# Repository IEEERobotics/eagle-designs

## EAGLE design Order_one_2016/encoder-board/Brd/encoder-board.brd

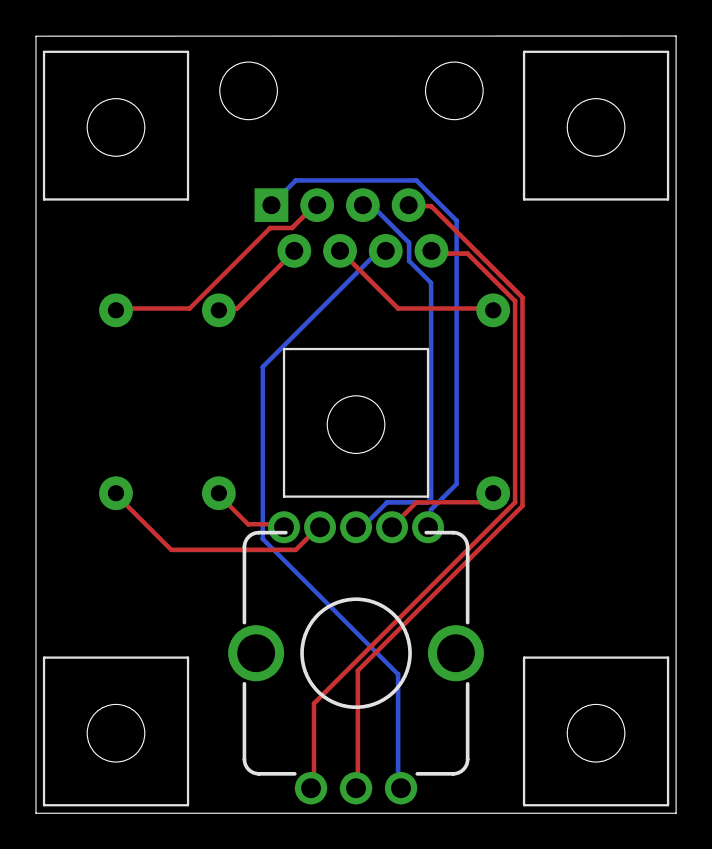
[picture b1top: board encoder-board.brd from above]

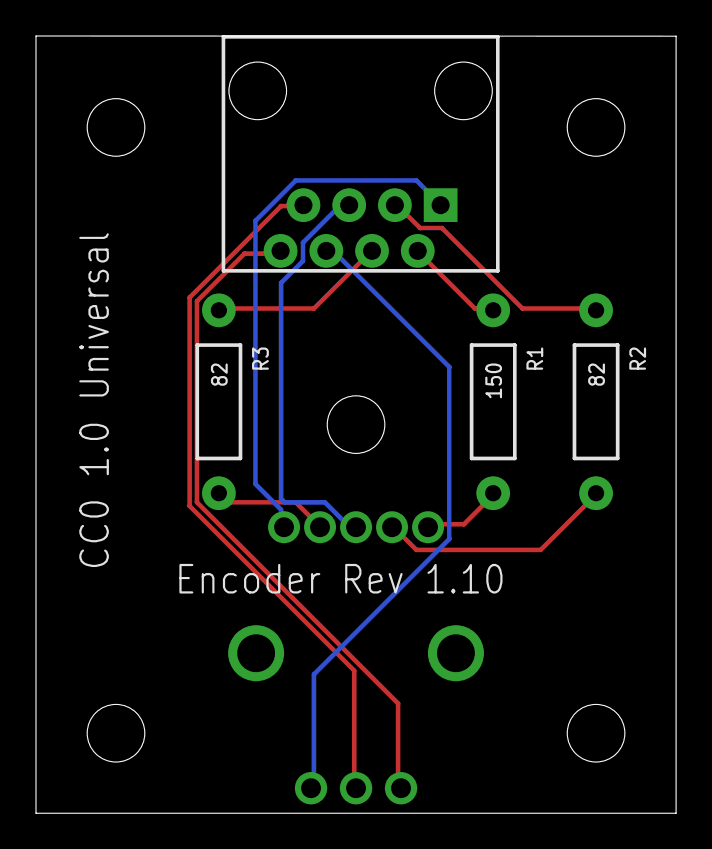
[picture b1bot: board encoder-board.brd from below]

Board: 2 copper layers, 35.6 x 43.2 mm, 10 parts (4 on the bottom side), 11 nets.

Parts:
J1: RJ45-8PTH; RJ45-8
MT1, MT2, MT3, MT4, MT5: 3.2-MOUNT
R1: 150; AXIAL-0.4
R2, R3: 82; AXIAL-0.4
SW2: SPARKFUN-COM-10982; ENCODER_LED_3

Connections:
BLUE: J1.4, R3.P$1
GREEN: J1.3, R2.P$1
LED-SWITCH-COM: J1.1, SW2.5
unnamed: R3.P$2, SW2.4
unnamed: R1.P$2, SW2.1
unnamed: R2.P$2, SW2.2
PUSHBUTTON: J1.5, SW2.3
QUAD-A: J1.8, SW2.A
QUAD-B: J1.6, SW2.B
QUAD-C: J1.7, SW2.C
RED: J1.2, R1.P$1

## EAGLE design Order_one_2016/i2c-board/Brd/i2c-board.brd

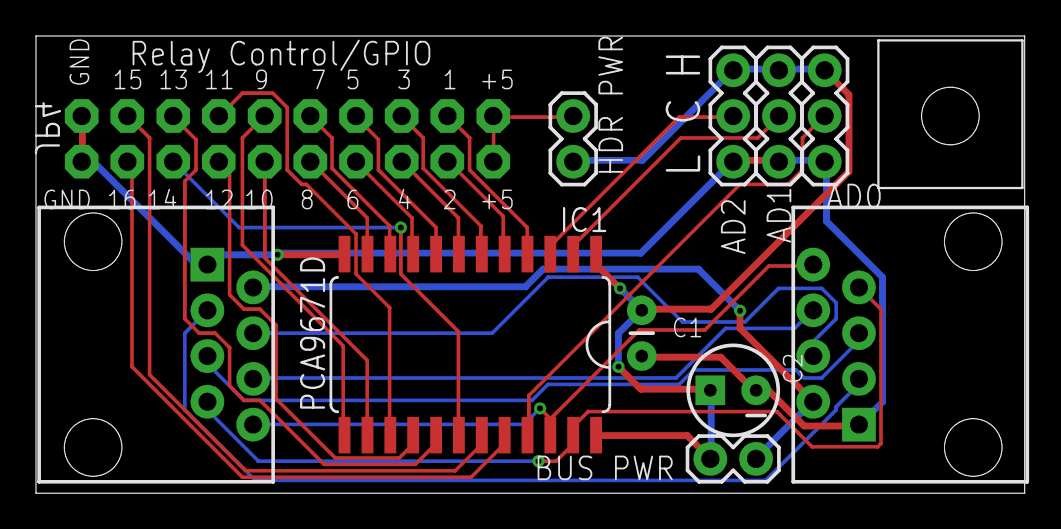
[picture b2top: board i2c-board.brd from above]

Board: 2 copper layers, 54.9 x 25.4 mm, 12 parts (1 on the bottom side), 29 nets.

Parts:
C1: .1uf; CAP-PTH-SMALL
C2: 10uf; CPOL-RADIAL-10UF-25V
IC1: PCA9671D; SOIC24
JP1: AD0; 1X03
JP2: AD1; 1X03
JP3: AD2; 1X03
JP4: Relay Control/GPIO; 2X10
JP5, JP6: RJ45-8PTH; RJ45-8
JP8: HDR PWR; 1X02
JP9: BUS PWR; 1X02
MT1: 3.2-MOUNT

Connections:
+5V: C1.2, C2.1, IC1.1, IC1.24, JP1.1, JP2.1, JP3.1, JP8.1, JP9.2
A0: JP5.3, JP6.3
A1: JP5.4, JP6.4
A2: JP5.5, JP6.5
A3: JP5.6, JP6.6
A4-SDA: IC1.23, JP5.7, JP6.7
A5-SCL: IC1.22, JP5.8, JP6.8
BUSS_VCC: JP5.2, JP6.2, JP9.1
GND: C1.1, C2.2, IC1.12, JP1.3, JP2.3, JP3.3, JP4.1, JP4.2, JP5.1, JP6.1
unnamed: JP4.19, JP4.20, JP8.2
unnamed: IC1.21, JP1.2
unnamed: IC1.2, JP2.2
unnamed: IC1.3, JP3.2
RL1: IC1.4, JP4.17
RL2: IC1.5, JP4.18
RL3: IC1.6, JP4.15
RL4: IC1.7, JP4.16
RL5: IC1.8, JP4.13
RL6: IC1.9, JP4.14
RL7: IC1.10, JP4.11
RL8: IC1.11, JP4.12
RL9: IC1.13, JP4.9
RL10: IC1.14, JP4.10
RL11: IC1.15, JP4.7
RL12: IC1.16, JP4.8
RL13: IC1.17, JP4.5
RL14: IC1.18, JP4.6
RL15: IC1.19, JP4.3
RL16: IC1.20, JP4.4

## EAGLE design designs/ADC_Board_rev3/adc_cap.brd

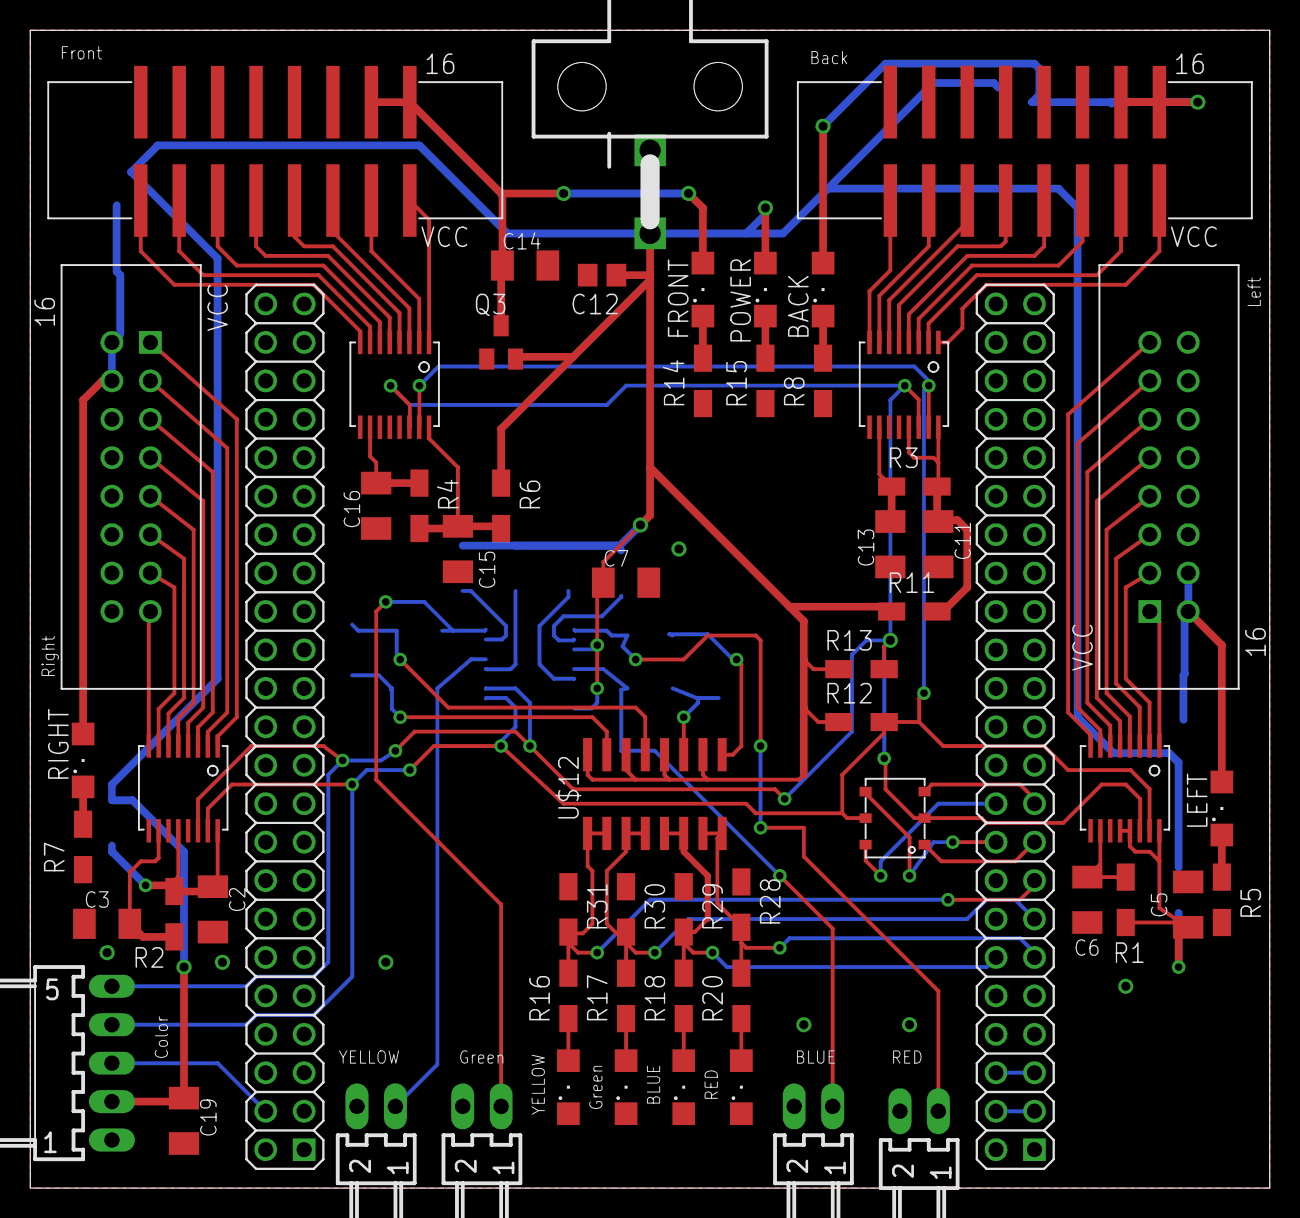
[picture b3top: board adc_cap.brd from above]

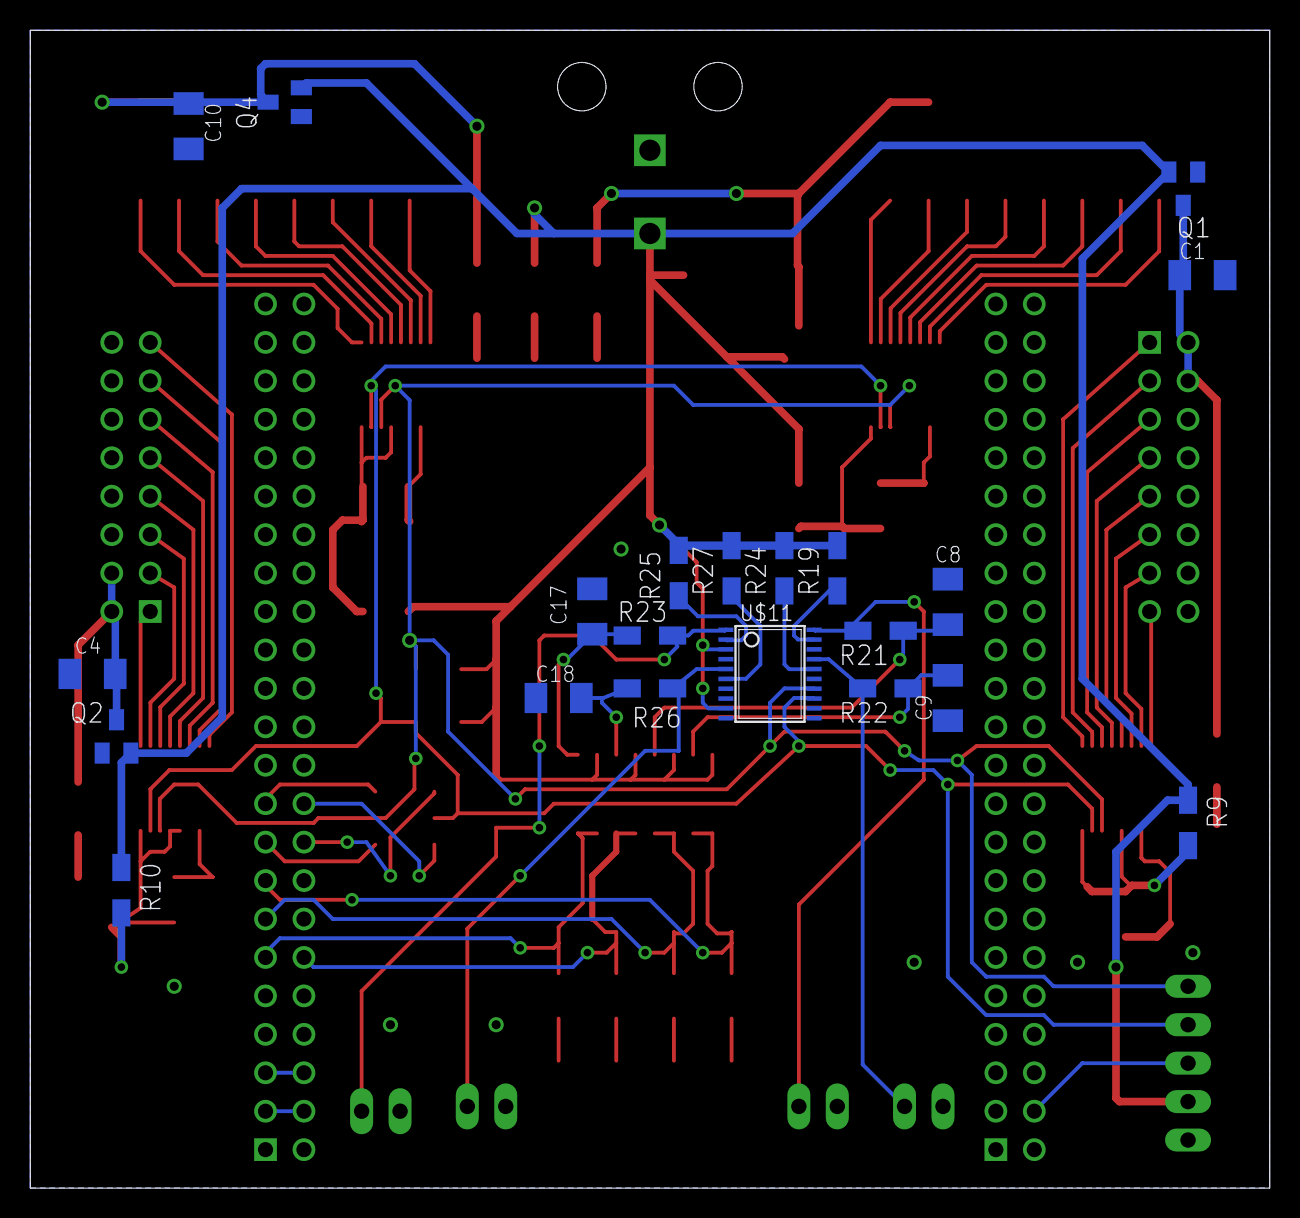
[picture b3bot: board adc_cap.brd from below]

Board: 2 copper layers, 81.9 x 76.5 mm, 81 parts (21 on the bottom side), 80 nets.

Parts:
BACK: SML1206
C1, C2, C4, C5, C7, C10, C14, C15, C19: 10uF; C1206K
C3, C13, C16: 0.1uF; C1206K
C6: 0.1F; C1206K
C8, C9, C17, C18: NC; C1206K
C11: 0K; C1206K
C12: 10uF; C0805
FRONT: SML1206
J1, J2, J3, J4: 22-05-7028-02; 7395-02
J5: 22-05-7058-05; 7395-05
LED6, LED7, LED8, LED9: SML1206
LEFT: SML1206
PL1: 5569-2
POWER: SML1206
Q1, Q2, Q3, Q4: BSS84; SOT23
R1, R2, R3, R4: NC; R1206W
R5, R7: 10K; R1206W
R6, R9, R11, R21, R22, R23, R26: 0K; R1206W
R8, R14, R15, R16, R17, R18, R19, R20, R24, R25, R27, R28, R29, R30, R31: 10k; R1206W
R10: 0k; R1206W
R12, R13: 5K; R1206W
RIGHT: SML1206
U$1: BBB_CAP; BBB
U$2, U$7: 3020-16-0300-00; 8X2_SMD_HEADER
U$3, U$4, U$6, U$8: ADS7830; ADC8_SD
U$5, U$9: 75869-103LF; 8X2_THROUGH_HOLE_HEADER
U$10: CAS-220TB; DPDT_DIP_SWITCH
U$11: ISL23348_SD; TSSOP-20
U$12: MMPQ2907A; SO1C-16

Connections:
GND: C1.2, C2.2, C3.1, C4.2, C5.2, C6.1, C7.2, C8.1, C9.1, C10.2, C11.2, C12.2, C13.1, C14.2, C15.2, C16.1, C17.1, C18.1, C19.2, J1.2, J2.2, J3.2, J4.2, J5.1, LED6.C, LED7.C, LED8.C, LED9.C, PL1.1, Q1.1, Q2.1, Q3.1, Q4.1, R5.1, R7.1, R8.1, R14.1, R28.1, R29.1, R30.1, R31.1, U$1.P8_1, U$1.P8_2, U$1.P9_1, U$1.P9_2, U$1.P9_43, U$1.P9_44, U$1.P9_45, U$1.P9_46, U$2.9, U$2.10, U$2.11, U$2.12, U$2.13, U$2.14, U$3.9, U$3.11, U$3.12, U$4.9, U$4.11, U$4.13, U$5.9, U$5.10, U$5.11, U$5.12, U$5.13, U$5.14, U$6.9, U$6.11, U$7.9, U$7.10, U$7.11, U$7.12, U$7.13, U$7.14, U$8.9, U$8.11, U$8.12, U$8.13, U$9.9, U$9.10, U$9.11, U$9.12, U$9.13, U$9.14, U$11.8, U$11.10, U$11.11, U$11.12
unnamed: U$2.1, U$3.1
unnamed: J5.4, R12.2, U$3.15, U$4.15, U$6.15, U$8.15, U$10.5, U$11.13
unnamed: U$2.2, U$3.2
unnamed: U$2.3, U$3.3
unnamed: U$2.4, U$3.4
unnamed: U$2.5, U$3.5
unnamed: U$2.6, U$3.6
unnamed: U$2.7, U$3.7
unnamed: U$2.8, U$3.8
unnamed: U$1.P9_18, U$10.4
unnamed: U$1.P9_20, U$10.6
unnamed: C13.2, R3.1, U$3.10
unnamed: J5.5, R13.2, U$3.14, U$4.14, U$6.14, U$8.14, U$10.2, U$11.14
unnamed: R19.1, U$11.19
unnamed: U$4.1, U$5.1
unnamed: U$4.2, U$5.2
unnamed: U$4.3, U$5.3
unnamed: U$4.4, U$5.4
unnamed: U$4.5, U$5.5
unnamed: U$4.6, U$5.6
unnamed: U$4.7, U$5.7
unnamed: U$4.8, U$5.8
unnamed: U$1.P9_17, U$10.1
unnamed: U$1.P9_19, U$10.3
unnamed: C11.1, R3.2, R11.2, U$3.13, U$3.16
unnamed: C3.2, R2.1, U$4.10
unnamed: C4.1, LEFT.A, Q2.3, U$9.15, U$9.16
unnamed: U$6.1, U$9.1
unnamed: U$6.2, U$9.2
unnamed: U$6.3, U$9.3
unnamed: U$6.4, U$9.4
unnamed: U$6.5, U$9.5
unnamed: U$6.6, U$9.6
unnamed: U$6.7, U$9.7
unnamed: U$6.8, U$9.8
unnamed: R24.1, U$11.16
unnamed: U$7.1, U$8.1
unnamed: C2.1, R2.2, R9.2, U$4.12, U$4.16
unnamed: C6.2, R1.1, U$6.10
unnamed: R25.1, U$11.2
unnamed: U$7.2, U$8.2
unnamed: U$7.3, U$8.3
unnamed: U$7.4, U$8.4
unnamed: U$7.5, U$8.5
unnamed: U$7.6, U$8.6
unnamed: U$7.7, U$8.7
unnamed: U$7.8, U$8.8
unnamed: C5.1, R1.2, R10.2, U$6.12, U$6.13, U$6.16
unnamed: LEFT.C, R5.2
unnamed: R27.1, U$11.6
unnamed: C15.1, R4.2, R6.2, U$8.16
unnamed: C16.2, R4.1, U$8.10
unnamed: C1.1, Q1.3, RIGHT.A, U$5.15, U$5.16
unnamed: R7.2, RIGHT.C
unnamed: BACK.A, C10.1, Q4.3, U$2.15, U$2.16
unnamed: BACK.C, R8.2
unnamed: C14.1, FRONT.A, Q3.3, U$7.15, U$7.16
unnamed: FRONT.C, R14.2
unnamed: LED8.A, R17.1
unnamed: POWER.C, R15.2
unnamed: J4.1, R23.2, U$11.1
unnamed: J3.1, R26.2, U$11.5
unnamed: J2.1, R22.2, U$11.17
unnamed: J1.1, R21.2, U$11.20
unnamed: LED9.A, R16.1
unnamed: LED7.A, R18.1
unnamed: LED6.A, R20.1
unnamed: C17.2, R23.1, U$12.9
unnamed: C18.2, R26.1, U$12.11
unnamed: C9.2, R22.1, U$12.15
unnamed: C8.2, R21.1, U$12.13
unnamed: J5.3, U$1.P8_4
unnamed: R17.2, R30.2, U$1.P9_13, U$12.3, U$12.4
unnamed: R20.2, R28.2, U$1.P9_11, U$12.7, U$12.8
unnamed: R18.2, R29.2, U$1.P9_12, U$12.5, U$12.6
unnamed: R16.2, R31.2, U$1.P9_15, U$12.1, U$12.2
VCC: C7.1, C12.1, C19.1, J5.2, PL1.2, POWER.A, Q1.2, Q2.2, Q3.2, Q4.2, R6.1, R9.1, R10.1, R11.1, R12.1, R13.1, R19.2, R24.2, R25.2, R27.2, U$11.3, U$11.9, U$12.10, U$12.12, U$12.14, U$12.16
VDD_3V3EXP: U$1.P9_3, U$1.P9_4
VDD_5V: U$1.P9_5, U$1.P9_6

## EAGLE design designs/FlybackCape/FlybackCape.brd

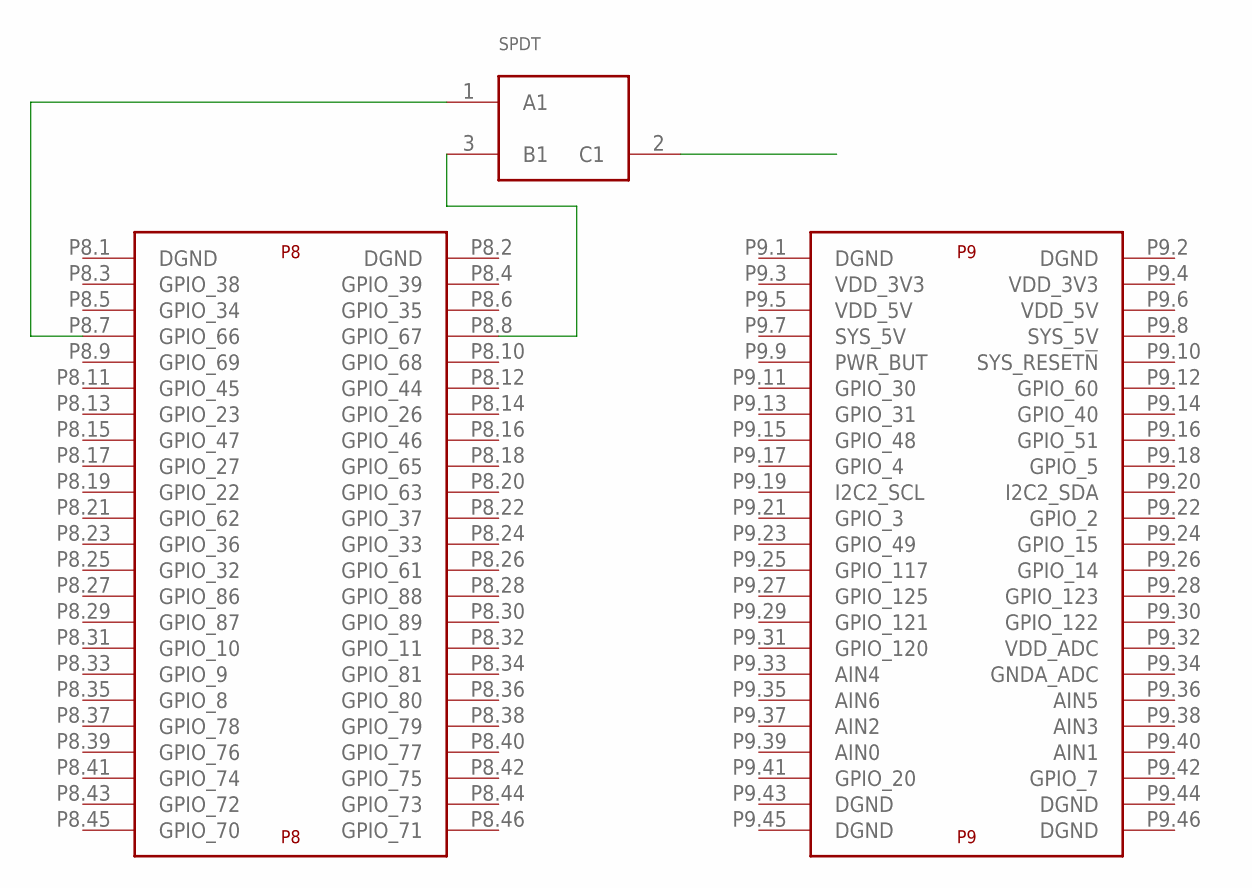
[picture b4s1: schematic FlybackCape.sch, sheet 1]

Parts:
SPDT: SPDT_SWITCH; SPDT
U$2: BEAGLE_BONE_BLACK_CAPE

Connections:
EN: SPDT.2 (C1); also elsewhere on the board
unnamed: SPDT.1 (A1), U$2.P8.7 (GPIO_66)
unnamed: SPDT.3 (B1), U$2.P8.8 (GPIO_67)

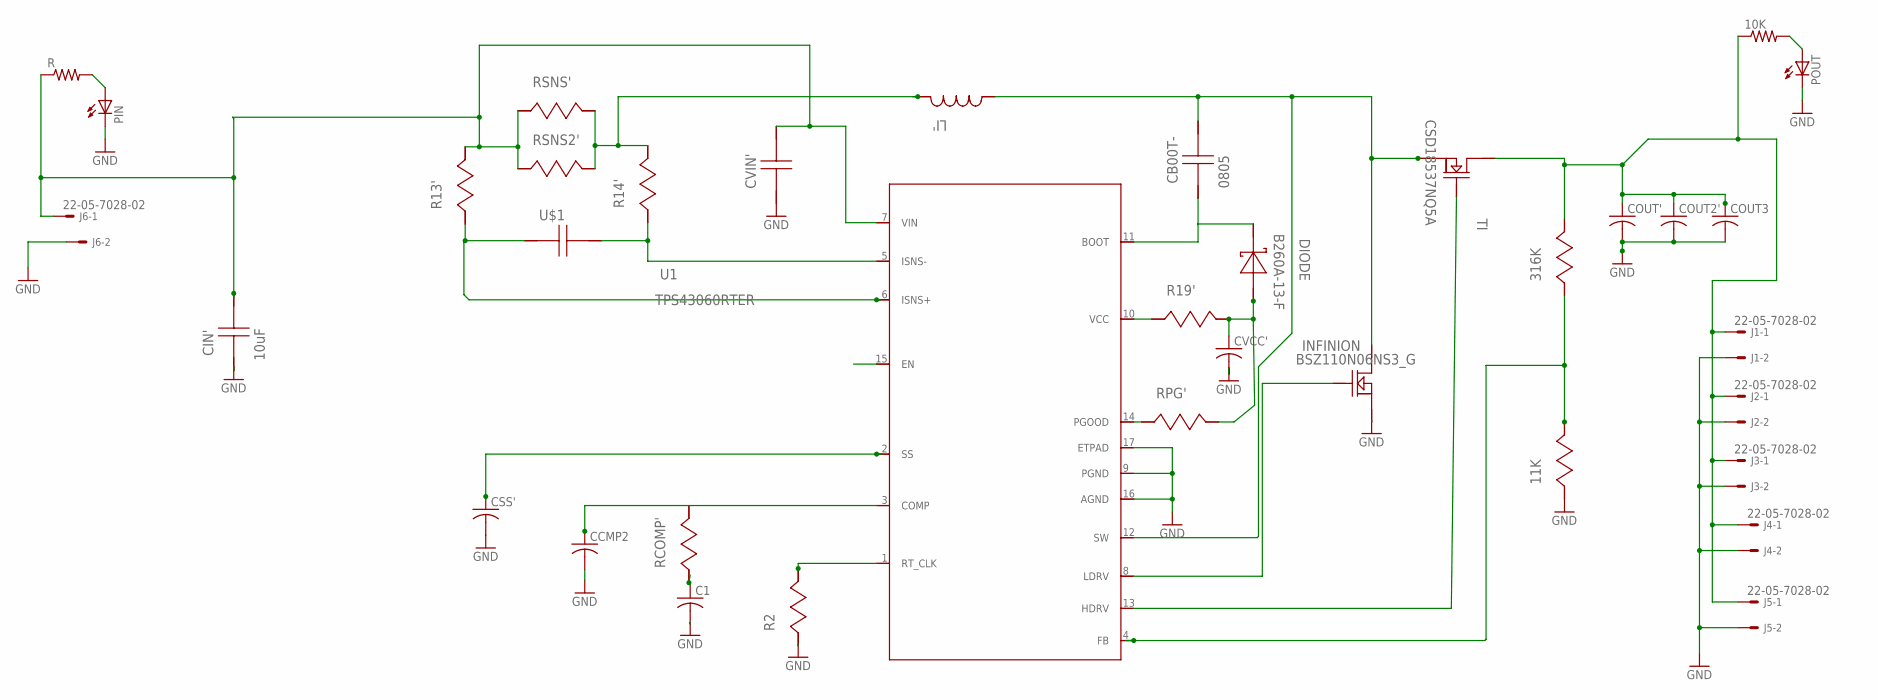
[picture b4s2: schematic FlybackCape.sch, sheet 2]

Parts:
10K: R-US_R1206; R1206
11K, 316K: CRCW0402110KFKED; 0402
C1: C-USC0805; C0805
CB00T-: 0805
CCMP2: C-USC0402; C0402
CIN': 10uF; 1210
COUT2', COUT3: C-USC1812; C1812
COUT': C-USC1812; C1812
CSS': C-USC0603K; C0603K
CVCC': C-USC0805; C0805
CVIN': 08053C104KAT2A; 0805
DIODE: B260A-13-F; SMA
INFINION: BSZ110N06NS3_G; PG-TSDSON-8
J1, J2, J3, J4, J5, J6: 22-05-7028-02; 7395-02
LI': MSS1210-153MEB; MSS1210
PIN: LEDCHIPLED_1206; CHIPLED_1206
POUT: LEDCHIPLED_1206; CHIPLED_1206
R: R-US_R1206; R1206
R2: CRCW04023K32FKED; 0402
R13', R14', R19': CRCW04022R00FKED; 0402
RCOMP': CRCW04023K32FKED; 0402
RPG': CRCW0402100KFKED; 0402
RSNS2': PRL1632-R012-F-T1; 1206
RSNS': PRL1632-R012-F-T1; 1206
TI: CSD18537NQ5A; TRANS_NEXFET_Q5A
U1: TPS43060RTER; S-PVQFN-N16
U$1: GRM188R61C106MA73D; 0603

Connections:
CSS: CSS'.1, U1.2 (SS)
EN: U1.15 (EN); also elsewhere on the board
GND: 11K.2, C1.2, CCMP2.2, CIN'.2, COUT2'.2, COUT3.2, COUT'.2, CSS'.2, CVCC'.2, CVIN'.2, INFINION.1 (SOURCE_2), INFINION.2 (SOURCE_2), INFINION.3 (SOURCE_2), J1.2, J2.2, J3.2, J4.2, J5.2, J6.2, PIN.C, POUT.C, R2.2, U1.9 (PGND), U1.16 (AGND), U1.17 (ETPAD)
LNEG: CB00T-.1, INFINION.5 (DRAIN_2), INFINION.6 (DRAIN_2), INFINION.7 (DRAIN_2), INFINION.8 (DRAIN_2), INFINION.9 (DRAIN_2), LI'.2, TI.1 (SOURCE_2), TI.2 (SOURCE_2), TI.3 (SOURCE_2), U1.12 (SW)
LPOS: LI'.1, R14'.1, RSNS2'.1, RSNS'.1
unnamed: INFINION.4 (GATE), U1.8 (LDRV)
unnamed: CB00T-.2, DIODE.1 (K), U1.11 (BOOT)
unnamed: CVCC'.1, DIODE.2 (A), R19'.1, RPG'.1
unnamed: R19'.2, U1.10 (VCC)
unnamed: RPG'.2, U1.14 (PGOOD)
unnamed: 10K.2, POUT.A
unnamed: PIN.A, R.2
unnamed: 11K.1, 316K.2, U1.4 (FB)
unnamed: C1.1, RCOMP'.2
unnamed: R14'.2, U1.5 (ISNS-), U$1.1
unnamed: R13'.2, U1.6 (ISNS+), U$1.2
unnamed: R2.1, U1.1 (RT_CLK)
unnamed: CCMP2.1, RCOMP'.1, U1.3 (COMP)
TI: TI.4 (GATE), U1.13 (HDRV)
VIN: CIN'.1, CVIN'.1, J6.1, R.1, R13'.1, RSNS2'.2, RSNS'.2, U1.7 (VIN)
VOUT: 10K.1, 316K.1, COUT2'.1, COUT3.1, COUT'.1, J1.1, J2.1, J3.1, J4.1, J5.1, TI.5 (DRAIN_2), TI.6 (DRAIN_2), TI.7 (DRAIN_2), TI.8 (DRAIN_2), TI.9 (DRAIN_2)

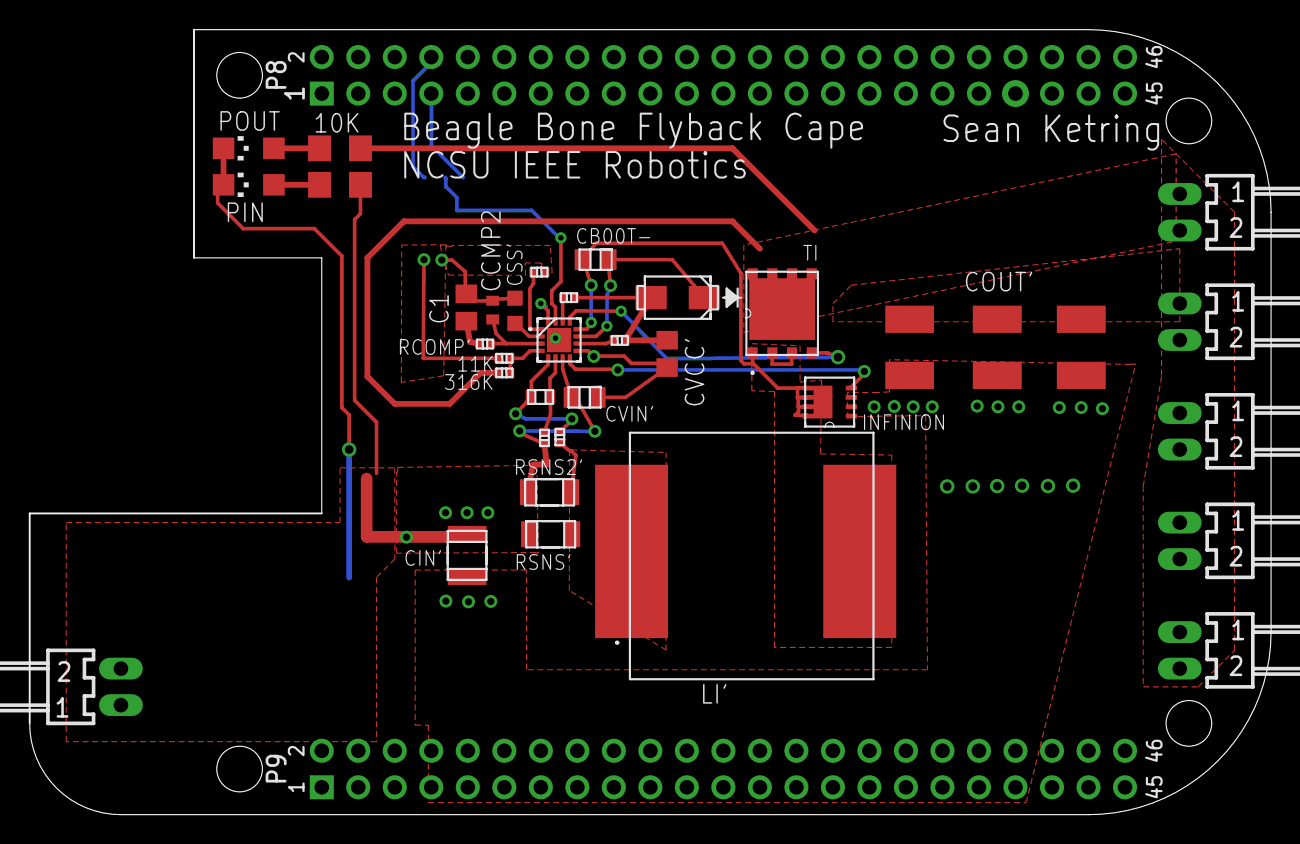
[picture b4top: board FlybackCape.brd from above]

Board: 2 copper layers, 86.4 x 54.6 mm, 38 parts (1 on the bottom side), 23 nets.

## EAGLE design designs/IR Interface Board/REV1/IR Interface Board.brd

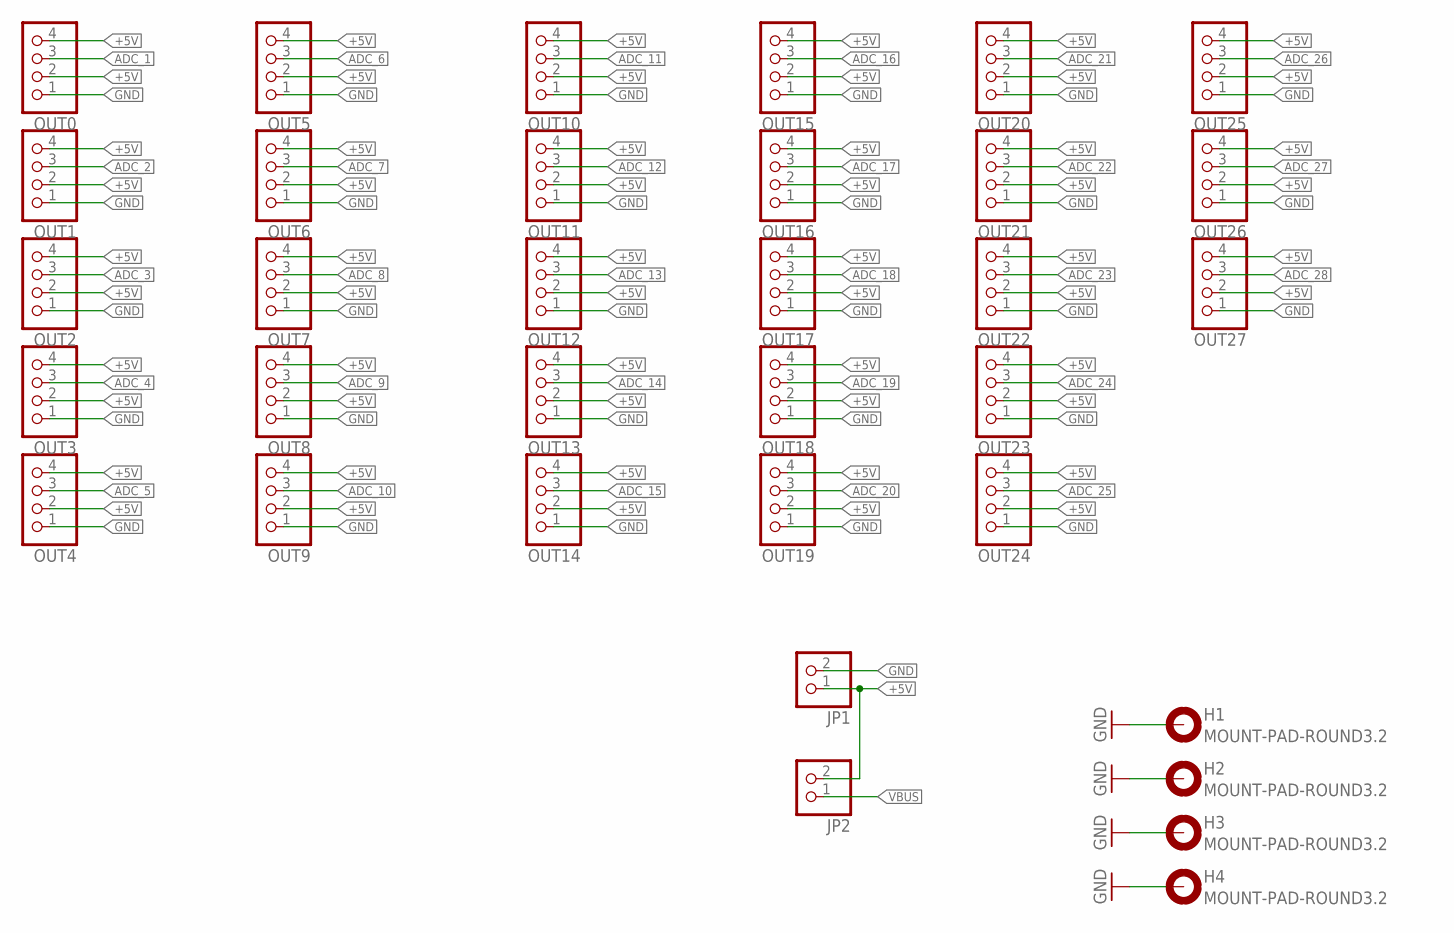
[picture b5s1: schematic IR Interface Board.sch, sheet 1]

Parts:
H1, H2, H3, H4: MOUNT-PAD-ROUND3.2; 3,2-PAD
JP1, JP2: PINHD-1X2; 1X02
OUT0, OUT1, OUT2, OUT3, OUT4, OUT5, OUT6, OUT7, OUT8, OUT9, OUT10, OUT11, OUT12, OUT13, OUT14, OUT15, OUT16, OUT17, OUT18, OUT19, OUT20, OUT21, OUT22, OUT23, OUT24, OUT25, OUT26, OUT27: PINHD-1X4; 1X04

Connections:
+5V: JP1.1, JP2.2, OUT0.2, OUT0.4, OUT1.2, OUT1.4, OUT2.2, OUT2.4, OUT3.2, OUT3.4, OUT4.2, OUT4.4, OUT5.2, OUT5.4, OUT6.2, OUT6.4, OUT7.2, OUT7.4, OUT8.2, OUT8.4, OUT9.2, OUT9.4, OUT10.2, OUT10.4, OUT11.2, OUT11.4, OUT12.2, OUT12.4, OUT13.2, OUT13.4, OUT14.2, OUT14.4, OUT15.2, OUT15.4, OUT16.2, OUT16.4, OUT17.2, OUT17.4, OUT18.2, OUT18.4, OUT19.2, OUT19.4, OUT20.2, OUT20.4, OUT21.2, OUT21.4, OUT22.2, OUT22.4, OUT23.2, OUT23.4, OUT24.2, OUT24.4, OUT25.2, OUT25.4, OUT26.2, OUT26.4, OUT27.2, OUT27.4; also elsewhere on the board
ADC_1: OUT0.3; also elsewhere on the board
ADC_2: OUT1.3; also elsewhere on the board
ADC_3: OUT2.3; also elsewhere on the board
ADC_4: OUT3.3; also elsewhere on the board
ADC_5: OUT4.3; also elsewhere on the board
ADC_6: OUT5.3; also elsewhere on the board
ADC_7: OUT6.3; also elsewhere on the board
ADC_8: OUT7.3; also elsewhere on the board
ADC_9: OUT8.3; also elsewhere on the board
ADC_10: OUT9.3; also elsewhere on the board
ADC_11: OUT10.3; also elsewhere on the board
ADC_12: OUT11.3; also elsewhere on the board
ADC_13: OUT12.3; also elsewhere on the board
ADC_14: OUT13.3; also elsewhere on the board
ADC_15: OUT14.3; also elsewhere on the board
ADC_16: OUT15.3; also elsewhere on the board
ADC_17: OUT16.3; also elsewhere on the board
ADC_18: OUT17.3; also elsewhere on the board
ADC_19: OUT18.3; also elsewhere on the board
ADC_20: OUT19.3; also elsewhere on the board
ADC_21: OUT20.3; also elsewhere on the board
ADC_22: OUT21.3; also elsewhere on the board
ADC_23: OUT22.3; also elsewhere on the board
ADC_24: OUT23.3; also elsewhere on the board
ADC_25: OUT24.3; also elsewhere on the board
ADC_26: OUT25.3; also elsewhere on the board
ADC_27: OUT26.3; also elsewhere on the board
ADC_28: OUT27.3; also elsewhere on the board
GND: H1.B3,2, H2.B3,2, H3.B3,2, H4.B3,2, JP1.2, OUT0.1, OUT1.1, OUT2.1, OUT3.1, OUT4.1, OUT5.1, OUT6.1, OUT7.1, OUT8.1, OUT9.1, OUT10.1, OUT11.1, OUT12.1, OUT13.1, OUT14.1, OUT15.1, OUT16.1, OUT17.1, OUT18.1, OUT19.1, OUT20.1, OUT21.1, OUT22.1, OUT23.1, OUT24.1, OUT25.1, OUT26.1, OUT27.1; also elsewhere on the board
VBUS: JP2.1; also elsewhere on the board

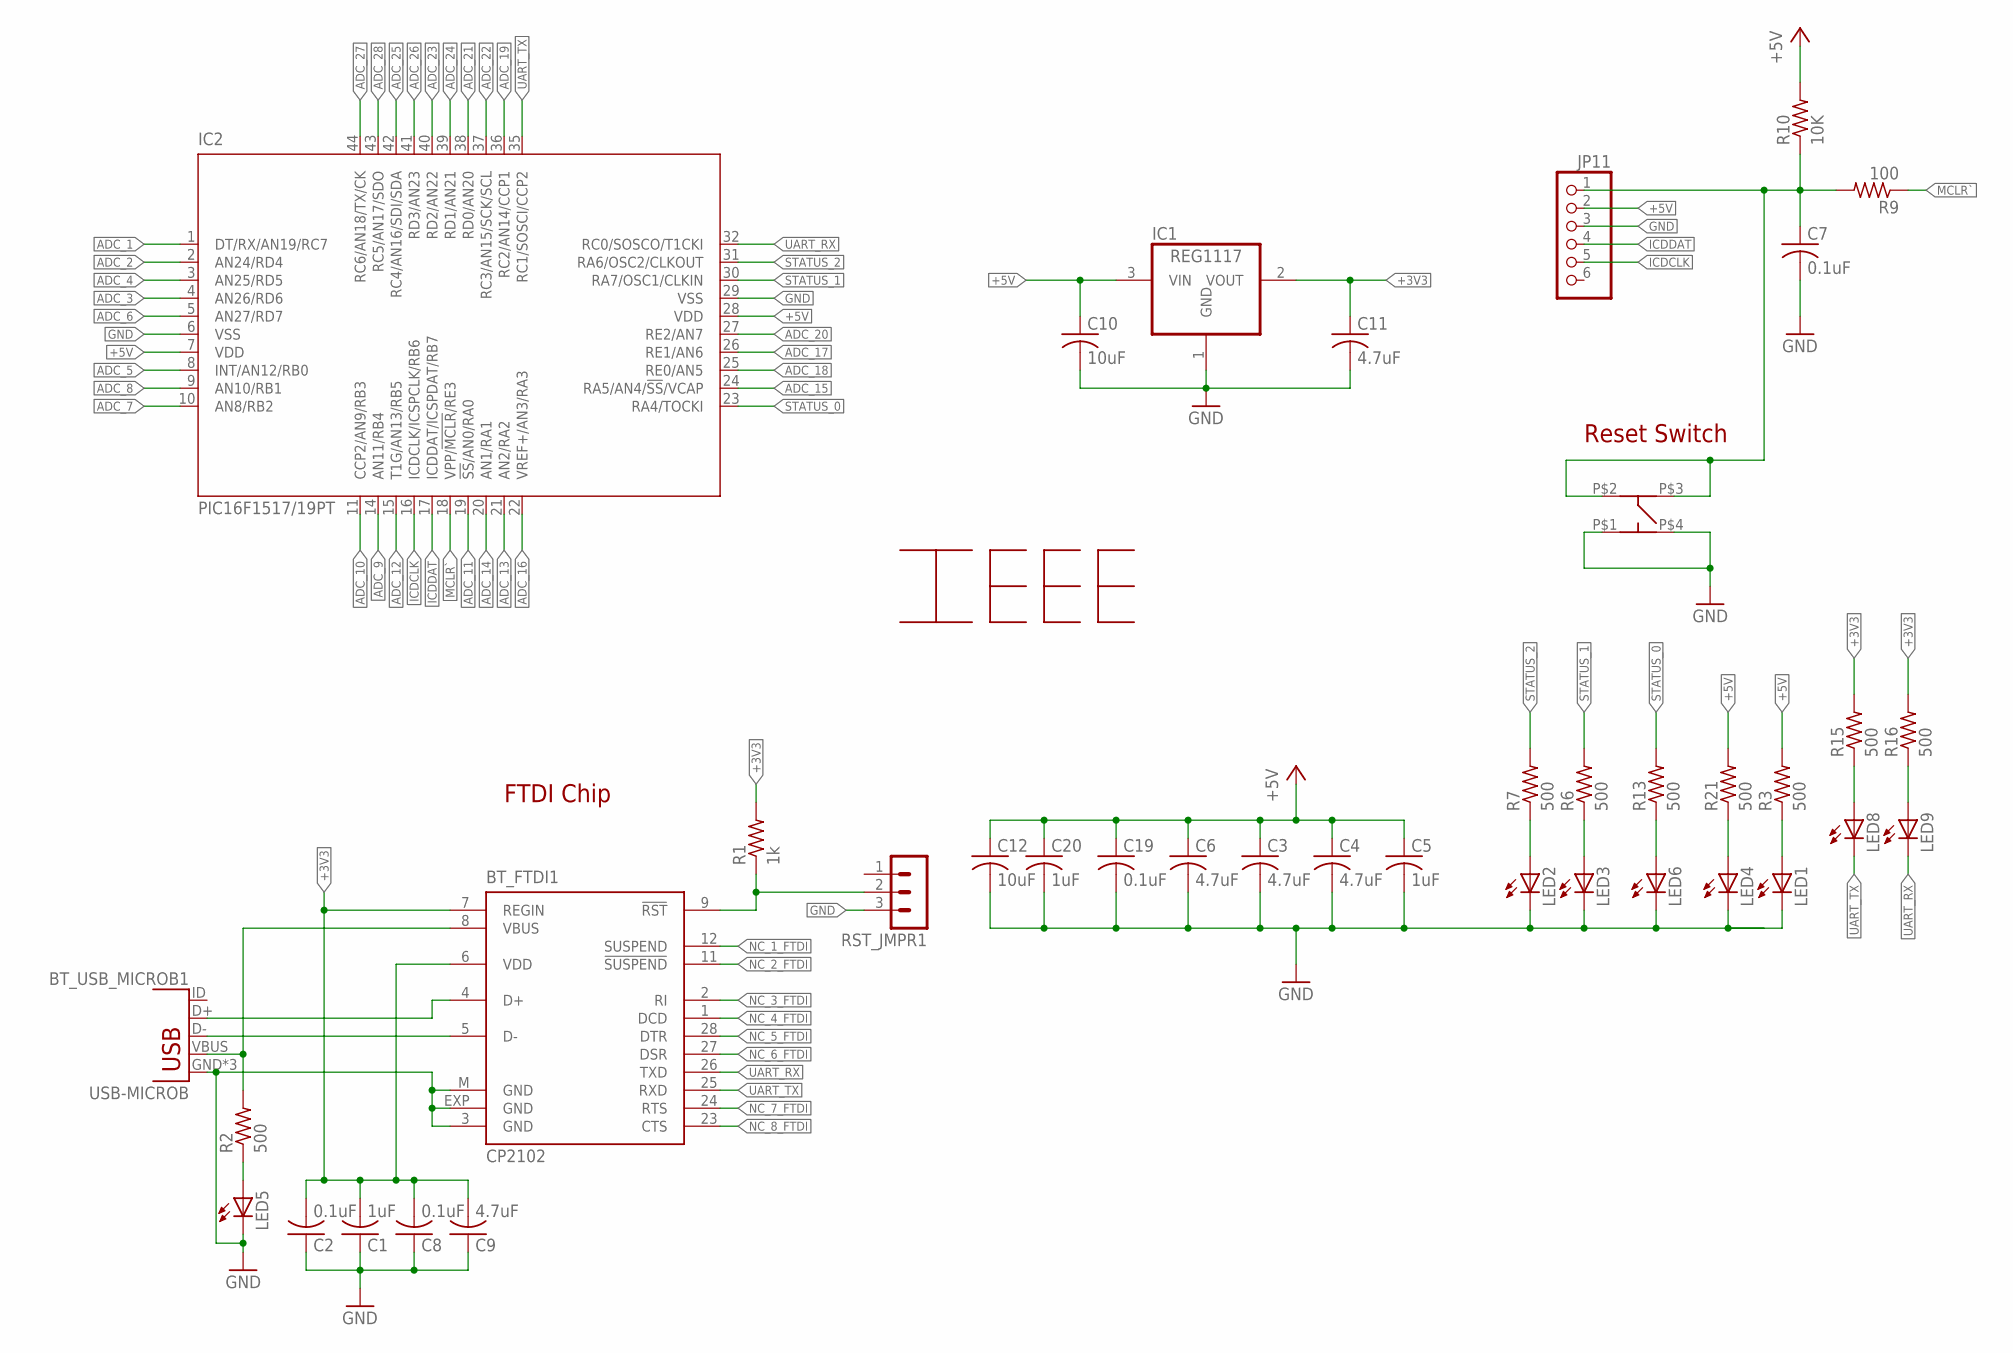
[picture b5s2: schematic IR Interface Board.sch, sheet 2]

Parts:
BT_FTDI1: CP2102; MLP28
BT_USB_MICROB1: USB-MICROB
C1, C5, C20: 1uF; C0805
C2, C7, C8, C19: 0.1uF; C0805
C3, C4, C6, C9, C11: 4.7uF; C0805
C10, C12: 10uF; C0805
IC1: REG1117; SOT223
IC2: PIC16F1517/19PT; TQFP44
JP11: PINHD-1X6/90; 1X06/90
LED1, LED2, LED3, LED4, LED5, LED6, LED8, LED9: LEDSML0603; SML0603
R1: 1k; R0805
R2, R3, R6, R7, R13, R15, R16, R21: 500; R0805
R9: 100; R0805
R10: 10K; R0805
RST_JMPR1: MA03-1
TOUCH_RESET: RESET; MC32882_FINAL
U$1: LOGO; IEEE-LOGO

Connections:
+3V3: BT_FTDI1.6 (VDD), BT_FTDI1.7 (REGIN), C1.2, C2.2, C8.2, C9.2, C11.1, IC1.2 (VOUT), R1.2, R15.2, R16.2
+5V: C3.1, C4.1, C5.1, C6.1, C10.1, C12.1, C19.1, C20.1, IC1.3 (VIN), IC2.7 (VDD), IC2.28 (VDD), JP11.2, R3.2, R10.2, R21.2; also elsewhere on the board
ADC_1: IC2.1 (DT/RX/AN19/RC7); also elsewhere on the board
ADC_2: IC2.2 (AN24/RD4); also elsewhere on the board
ADC_3: IC2.4 (AN26/RD6); also elsewhere on the board
ADC_4: IC2.3 (AN25/RD5); also elsewhere on the board
ADC_5: IC2.8 (INT/AN12/RB0); also elsewhere on the board
ADC_6: IC2.5 (AN27/RD7); also elsewhere on the board
ADC_7: IC2.10 (AN8/RB2); also elsewhere on the board
ADC_8: IC2.9 (AN10/RB1); also elsewhere on the board
ADC_9: IC2.14 (AN11/RB4); also elsewhere on the board
ADC_10: IC2.11 (CCP2/AN9/RB3); also elsewhere on the board
ADC_11: IC2.19 (!SS!/AN0/RA0); also elsewhere on the board
ADC_12: IC2.15 (T1G/AN13/RB5); also elsewhere on the board
ADC_13: IC2.21 (AN2/RA2); also elsewhere on the board
ADC_14: IC2.20 (AN1/RA1); also elsewhere on the board
ADC_15: IC2.24 (RA5/AN4/!SS!/VCAP); also elsewhere on the board
ADC_16: IC2.22 (VREF+/AN3/RA3); also elsewhere on the board
ADC_17: IC2.26 (RE1/AN6); also elsewhere on the board
ADC_18: IC2.25 (RE0/AN5); also elsewhere on the board
ADC_19: IC2.36 (RC2/AN14/CCP1); also elsewhere on the board
ADC_20: IC2.27 (RE2/AN7); also elsewhere on the board
ADC_21: IC2.38 (RD0/AN20); also elsewhere on the board
ADC_22: IC2.37 (RC3/AN15/SCK/SCL); also elsewhere on the board
ADC_23: IC2.40 (RD2/AN22); also elsewhere on the board
ADC_24: IC2.39 (RD1/AN21); also elsewhere on the board
ADC_25: IC2.42 (RC4/AN16/SDI/SDA); also elsewhere on the board
ADC_26: IC2.41 (RD3/AN23); also elsewhere on the board
ADC_27: IC2.44 (RC6/AN18/TX/CK); also elsewhere on the board
ADC_28: IC2.43 (RC5/AN17/SDO); also elsewhere on the board
BT_D+1: BT_FTDI1.4 (D+), BT_USB_MICROB1.D+
BT_D-1: BT_FTDI1.5 (D-), BT_USB_MICROB1.D-
GND: BT_FTDI1.3 (GND), BT_FTDI1.EXP (GND), BT_FTDI1.M (GND), BT_USB_MICROB1.GND, BT_USB_MICROB1.MT1 (GND), BT_USB_MICROB1.MT2 (GND), C1.1, C2.1, C3.2, C4.2, C5.2, C6.2, C7.2, C8.1, C9.1, C10.2, C11.2, C12.2, C19.2, C20.2, IC1.1 (GND), IC2.6 (VSS), IC2.29 (VSS), JP11.3, LED1.C, LED2.C, LED3.C, LED4.C, LED5.C, LED6.C, RST_JMPR1.3, TOUCH_RESET.P$1 (P1), TOUCH_RESET.P$4 (P4); also elsewhere on the board
ICDCLK: IC2.16 (ICDCLK/ICSPCLK/RB6), JP11.5
ICDDAT: IC2.17 (ICDDAT/ICSPDAT/RB7), JP11.4
MCLR: C7.1, JP11.1, R9.2, R10.1, TOUCH_RESET.P$2 (P2), TOUCH_RESET.P$3 (P3)
MCLR`: IC2.18 (VPP/!MCLR!/RE3), R9.1
unnamed: LED3.A, R6.1
unnamed: BT_FTDI1.9 (!RST), R1.1, RST_JMPR1.2
unnamed: LED6.A, R13.1
unnamed: LED1.A, R3.1
unnamed: LED2.A, R7.1
unnamed: LED4.A, R21.1
unnamed: LED8.A, R15.1
unnamed: LED9.A, R16.1
unnamed: LED5.A, R2.1
NC_1_FTDI: BT_FTDI1.12 (SUSPEND)
NC_2_FTDI: BT_FTDI1.11 (!SUSPEND)
NC_3_FTDI: BT_FTDI1.2 (RI)
NC_4_FTDI: BT_FTDI1.1 (DCD)
NC_5_FTDI: BT_FTDI1.28 (DTR)
NC_6_FTDI: BT_FTDI1.27 (DSR)
NC_7_FTDI: BT_FTDI1.24 (RTS)
NC_8_FTDI: BT_FTDI1.23 (CTS)
STATUS_0: IC2.23 (RA4/TOCKI), R13.2
STATUS_1: IC2.30 (RA7/OSC1/CLKIN), R6.2
STATUS_2: IC2.31 (RA6/OSC2/CLKOUT), R7.2
UART_RX: BT_FTDI1.26 (TXD), IC2.32 (RC0/SOSCO/T1CKI), LED9.C
UART_TX: BT_FTDI1.25 (RXD), IC2.35 (RC1/SOSCI/CCP2), LED8.C
VBUS: BT_FTDI1.8 (VBUS), BT_USB_MICROB1.VBUS, R2.2; also elsewhere on the board

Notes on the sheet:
Reset Switch
FTDI Chip

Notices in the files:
Order_one_2016/encoder-board/Brd/encoder-board.brd:
CC0 1.0 Universal
Order_one_2016/i2c-board/Brd/i2c-board.brd:
CC-BY-SA 4.0
parts and their libraries:
SparkFun-Resistors: Licensing: CC v3.0 Share-Alike You are welcome to use this library for commercial purposes.
SparkFun-Aesthetics: Licensing: Creative Commons ShareAlike 4.0 International - https://creativecommons.org/licenses/by-sa/4.0
